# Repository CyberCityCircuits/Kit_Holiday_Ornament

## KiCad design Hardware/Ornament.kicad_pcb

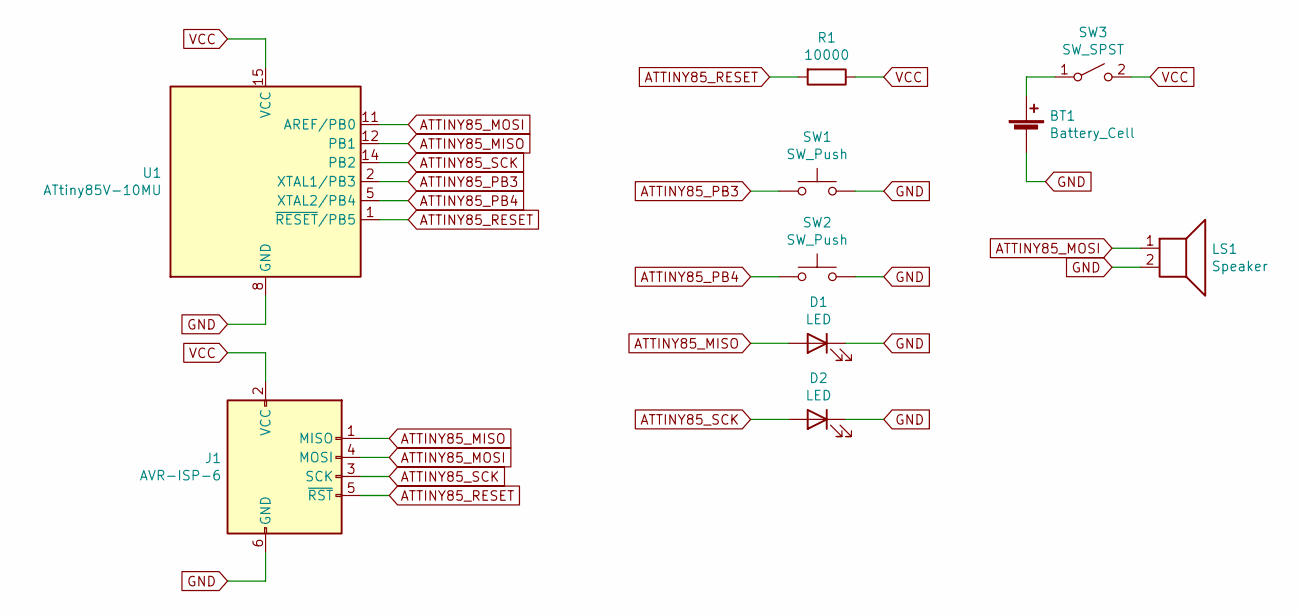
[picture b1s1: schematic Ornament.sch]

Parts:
BT1: Battery_Cell; Schematic - Battery CR2032
D1, D2: LED; Schematic - LED 5mm(2.56P) 003
J1: AVR-ISP-6; PinSocket_2x03_P2.54mm_Vertical
LS1: Speaker; Speaker_Large_Fuet
R1: 10000; R_0603
SW1, SW2: SW_Push; Schematic_-_Button_Labeled
SW3: SW_SPST; PinHeader_1x03_P2.54mm_Vertical
U1: ATtiny85V-10MU; QFN-20-1EP_4x4mm_P0.5mm_EP2.6x2.6mm

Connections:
ATTINY85_MISO: D1.2 (A), J1.1 (MISO), U1.12 (PB1)
ATTINY85_MOSI: J1.4 (MOSI), LS1.1, U1.11 (AREF/PB0)
ATTINY85_PB3: SW1.1, U1.2 (XTAL1/PB3)
ATTINY85_PB4: SW2.1, U1.5 (XTAL2/PB4)
ATTINY85_RESET: J1.5 (~RST), R1.2, U1.1 (~RESET~/PB5)
ATTINY85_SCK: D2.2 (A), J1.3 (SCK), U1.14 (PB2)
GND: BT1.2 (-), D1.1 (K), D2.1 (K), J1.6 (GND), LS1.2, SW1.2, SW2.2, U1.8 (GND), U1.21 (GND)
unnamed: BT1.1 (+), SW3.1 (A)
VCC: J1.2 (VCC), R1.1, SW3.2 (B), U1.15 (VCC)

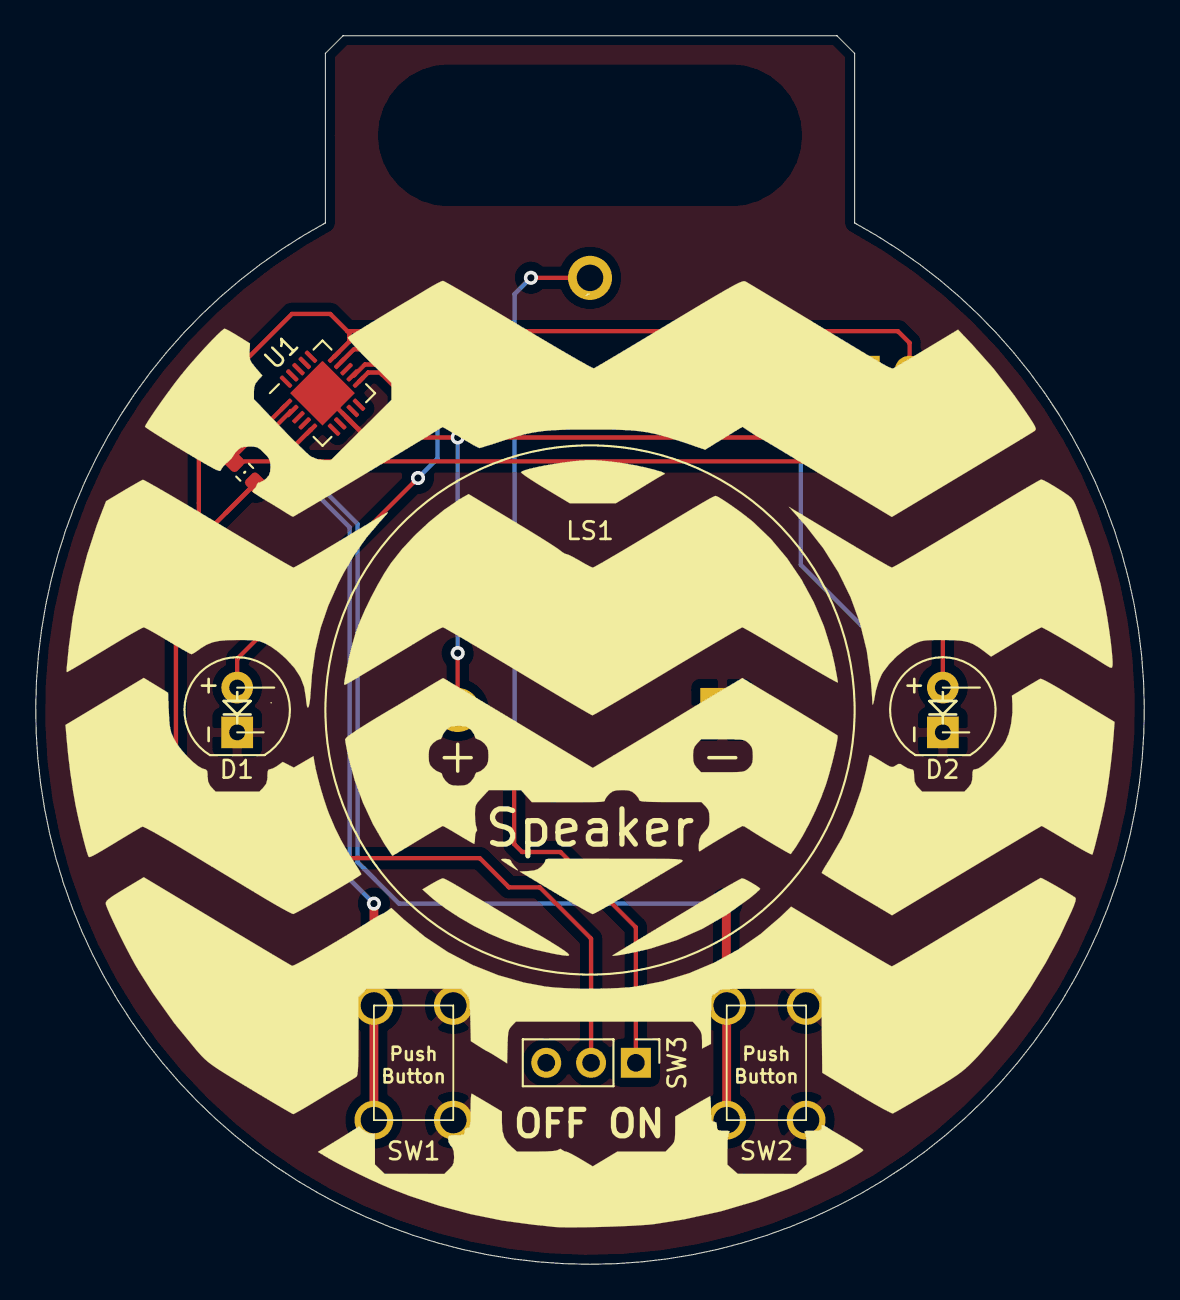
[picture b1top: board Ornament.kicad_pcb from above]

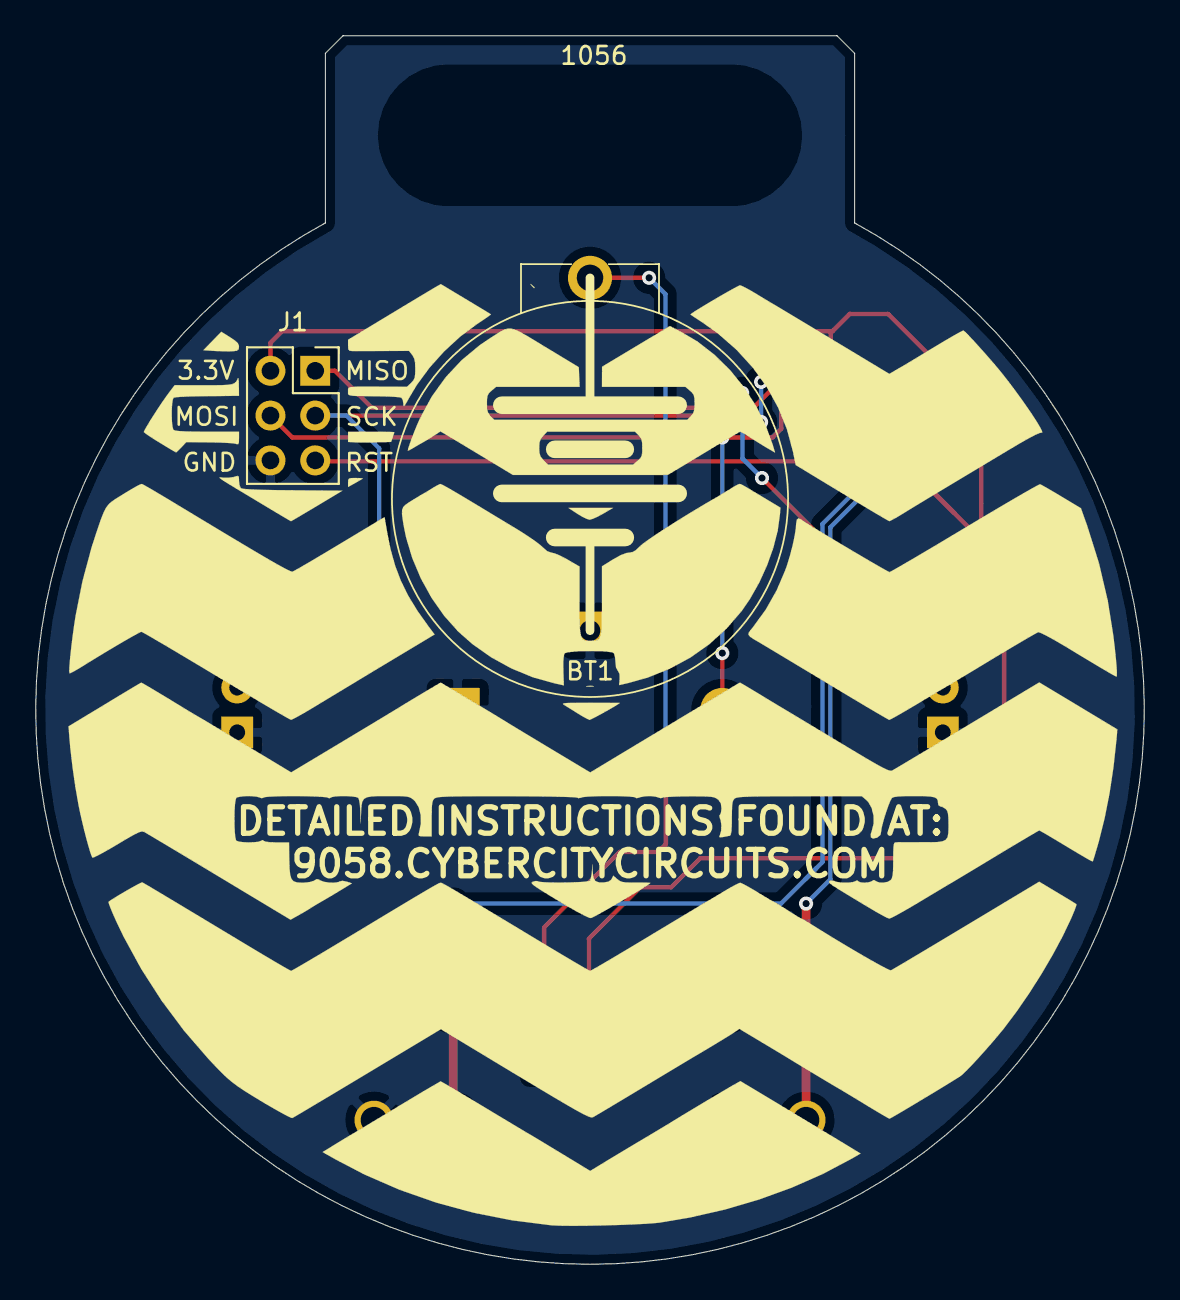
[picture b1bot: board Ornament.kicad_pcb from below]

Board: 2 copper layers, 62.8 x 69.6 mm, 11 parts (3 on the bottom side), 9 nets.

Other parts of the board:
Back: LOGO; Ornament Back 2020
